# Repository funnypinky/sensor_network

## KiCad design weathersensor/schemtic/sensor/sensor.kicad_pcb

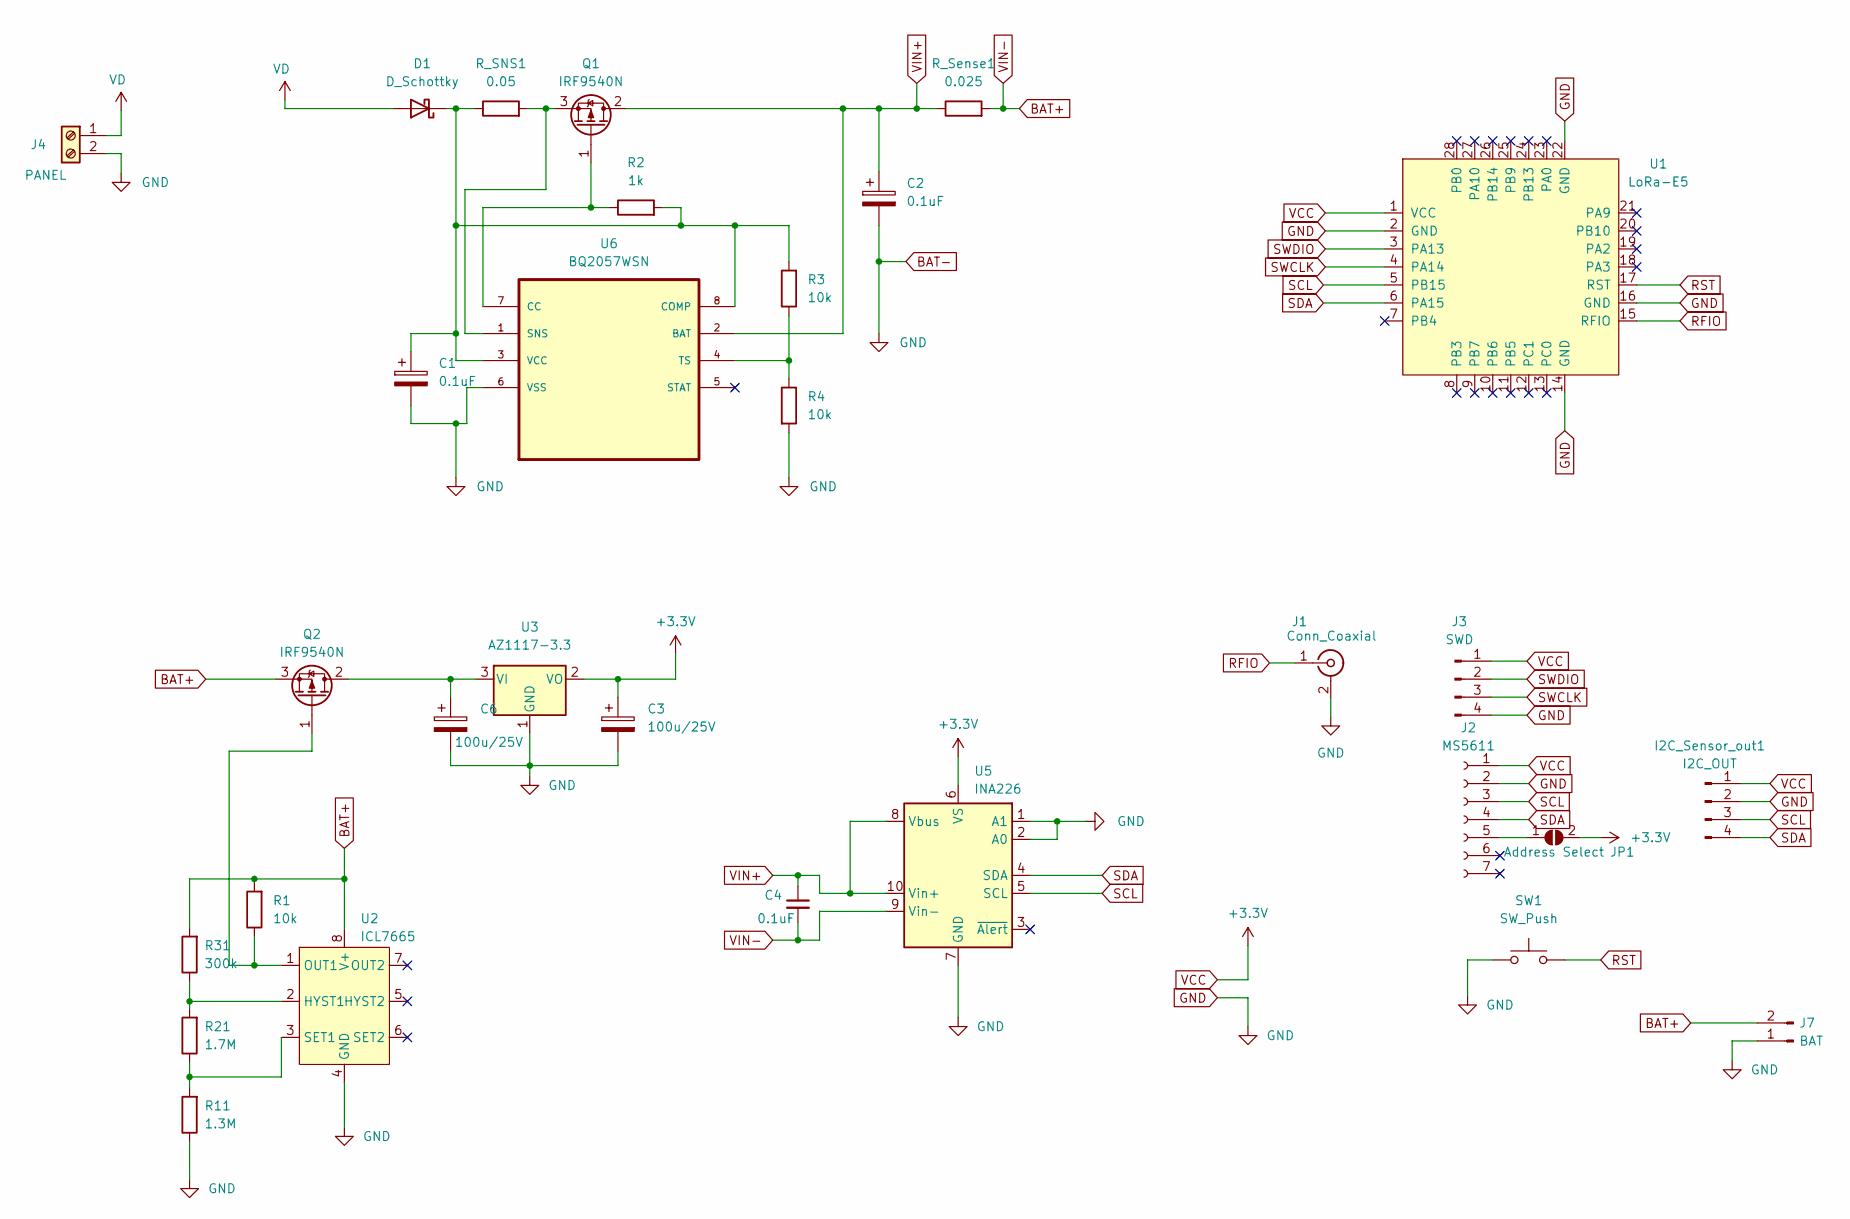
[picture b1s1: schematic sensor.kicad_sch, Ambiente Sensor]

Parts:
C1, C2, C4: 0.1uF; C_Rect_L4.6mm_W2.0mm_P2.50mm_MKS02_FKP02
C3, C6: 100u/25V; CP_Radial_D5.0mm_P2.50mm
D1: D_Schottky; D_SOD-123
I2C_Sensor_out1: I2C_OUT; JST_XH_B4B-XH-AM_1x04_P2.50mm_Vertical
J1: Conn_Coaxial; SMA_Amphenol_132203-12_Horizontal
J2: MS5611; PinHeader_1x07_P2.54mm_Vertical
J3: SWD; JST_XH_B4B-XH-AM_1x04_P2.50mm_Vertical
J4: PANEL; TerminalBlock_RND_205-00012_1x02_P5.00mm_Horizontal
J7: BAT; JST_EH_S2B-EH_1x02_P2.50mm_Horizontal
JP1: Address Select; SolderJumper-2_P1.3mm_Open_RoundedPad1.0x1.5mm
Q1, Q2: IRF9540N; TO-220-3_Horizontal_TabDown
R1, R3, R4: 10k; R_Axial_DIN0207_L6.3mm_D2.5mm_P10.16mm_Horizontal
R2: 1k; R_Axial_DIN0207_L6.3mm_D2.5mm_P10.16mm_Horizontal
R11: 1.3M; R_Axial_DIN0207_L6.3mm_D2.5mm_P10.16mm_Horizontal
R21: 1.7M; R_Axial_DIN0207_L6.3mm_D2.5mm_P10.16mm_Horizontal
R31: 300k; R_Axial_DIN0207_L6.3mm_D2.5mm_P10.16mm_Horizontal
R_SNS1: 0.05; R_2512_6332Metric
R_Sense1: 0.025; R_2512_6332Metric
SW1: SW_Push; SW_SPST_CK_RS282G05A3
U1: LoRa-E5
U2: ICL7665; DIP-8_W7.62mm_LongPads
U3: AZ1117-3.3; SOT-223
U5: INA226; VSSOP-10_3x3mm_P0.5mm
U6: BQ2057WSN; SOIC127P599X175-8N

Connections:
BAT+: C4.2, J7.2, Q2.3 (S), R1.2, R31.2, R_Sense1.2, U2.8 (V+), U5.9 (Vin-)
BAT-: C1.2, C2.2, C3.2, C6.2, I2C_Sensor_out1.2, J1.2 (Ext), J2.2, J3.4, J4.2, J7.1, R4.2, R11.1, SW1.1, U1.2 (GND), U1.14 (GND), U1.16 (GND), U1.22 (GND), U2.4 (GND), U3.1 (GND), U5.1 (A1), U5.2 (A0), U5.7 (GND), U6.6 (VSS)
unnamed: C1.1, D1.1 (K), R2.2, R3.2, R_SNS1.1, U6.3 (VCC), U6.8 (COMP)
unnamed: J2.5, JP1.1 (A)
unnamed: Q1.1 (G), R2.1, U6.7 (CC)
unnamed: Q1.3 (S), R_SNS1.2, U6.1 (SNS)
unnamed: C6.1, Q2.2 (D), U3.3 (VI)
unnamed: Q2.1 (G), R1.1, U2.1 (OUT1)
unnamed: R21.2, R31.1, U2.2 (HYST1)
unnamed: R11.2, R21.1, U2.3 (SET1)
unnamed: R3.1, R4.1, U6.4 (TS)
RFIO: J1.1 (In), U1.15 (RFIO)
RST: SW1.2, U1.17 (RST)
SCL: I2C_Sensor_out1.3, J2.3, U1.5 (PB15), U5.5 (SCL)
SDA: I2C_Sensor_out1.4, J2.4, U1.6 (PA15), U5.4 (SDA)
SWCLK: J3.3, U1.4 (PA14)
SWDIO: J3.2, U1.3 (PA13)
VCC: C3.1, I2C_Sensor_out1.1, J2.1, J3.1, JP1.2 (B), U1.1 (VCC), U3.2 (VO), U5.6 (VS)
VD: D1.2 (A), J4.1
VIN+: C2.1, C4.1, Q1.2 (D), R_Sense1.1, U5.8 (Vbus), U5.10 (Vin+), U6.2 (BAT)

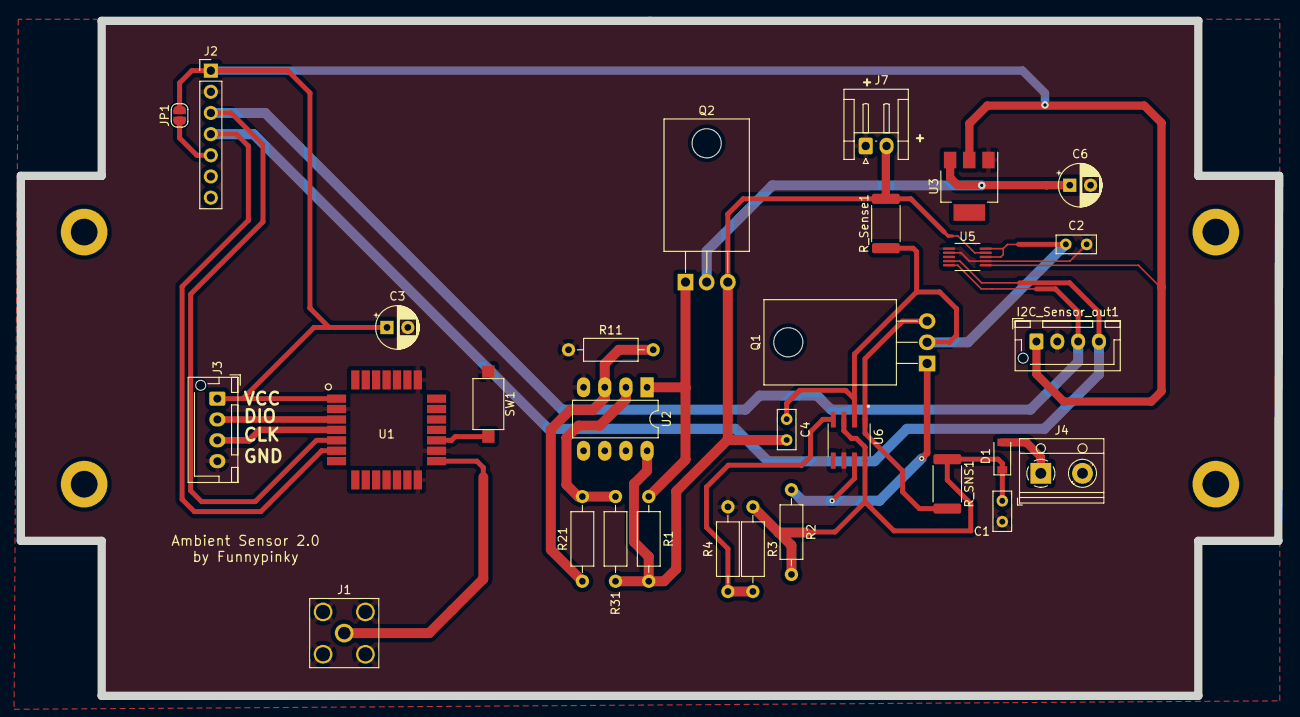
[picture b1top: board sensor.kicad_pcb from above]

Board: 2 copper layers, 151.0 x 81.0 mm, 30 parts (0 on the bottom side), 20 nets.

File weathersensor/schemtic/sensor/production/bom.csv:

Designator,Footprint,Quantity,Value,LCSC Part #
"C1, C2",1206,2,0.1u,
"C3, C6",C_Elec_6.3x7.7,2,100u/25V,
C4,1206,1,0.1uF,
D1,D_SOD-123,1,D_Schottky,
I2C_SENSOR_OUT1,JST_XH_B4B-XH-AM_1x04_P2.50mm_Vertical,1,I2C_OUT,
J1,SMA_Amphenol_132203-12_Horizontal,1,Conn_Coaxial,
J2,PinHeader_1x07_P2.54mm_Vertical,1,MS5611,
J3,JST_XH_B4B-XH-AM_1x04_P2.50mm_Vertical,1,SWD,
J4,TerminalBlock_RND_205-00012_1x02_P5.00mm_Horizontal,1,PANEL,
J7,JST_EH_S2B-EH_1x02_P2.50mm_Horizontal,1,BAT,
JP1,SolderJumper-2_P1.3mm_Open_RoundedPad1.0x1.5mm,1,Address Select,
"Q1, Q2",TO-263-2,2,IRF9540N,
"R1, R3, R4",2512,3,10k,
R11,2512,1,1.3M,
R2,2512,1,1k,
R21,2512,1,1.7M,
R31,2512,1,300k,
R_SENSE1,2512,1,0.025,
R_SNS1,2512,1,0.05,
SW1,SW_SPST_CK_RS282G05A3,1,SW_Push,
U1,LoRa-E5,1,LoRa-E5,
U2,SOIC-8_3.9x4.9mm_P1.27mm,1,ICL7665,
U3,SOT-223,1,AZ1117-3.3,
U5,VSSOP-10_3x3mm_P0.5mm,1,INA226,
U6,SOIC127P599X175-8N,1,BQ2057WSN,

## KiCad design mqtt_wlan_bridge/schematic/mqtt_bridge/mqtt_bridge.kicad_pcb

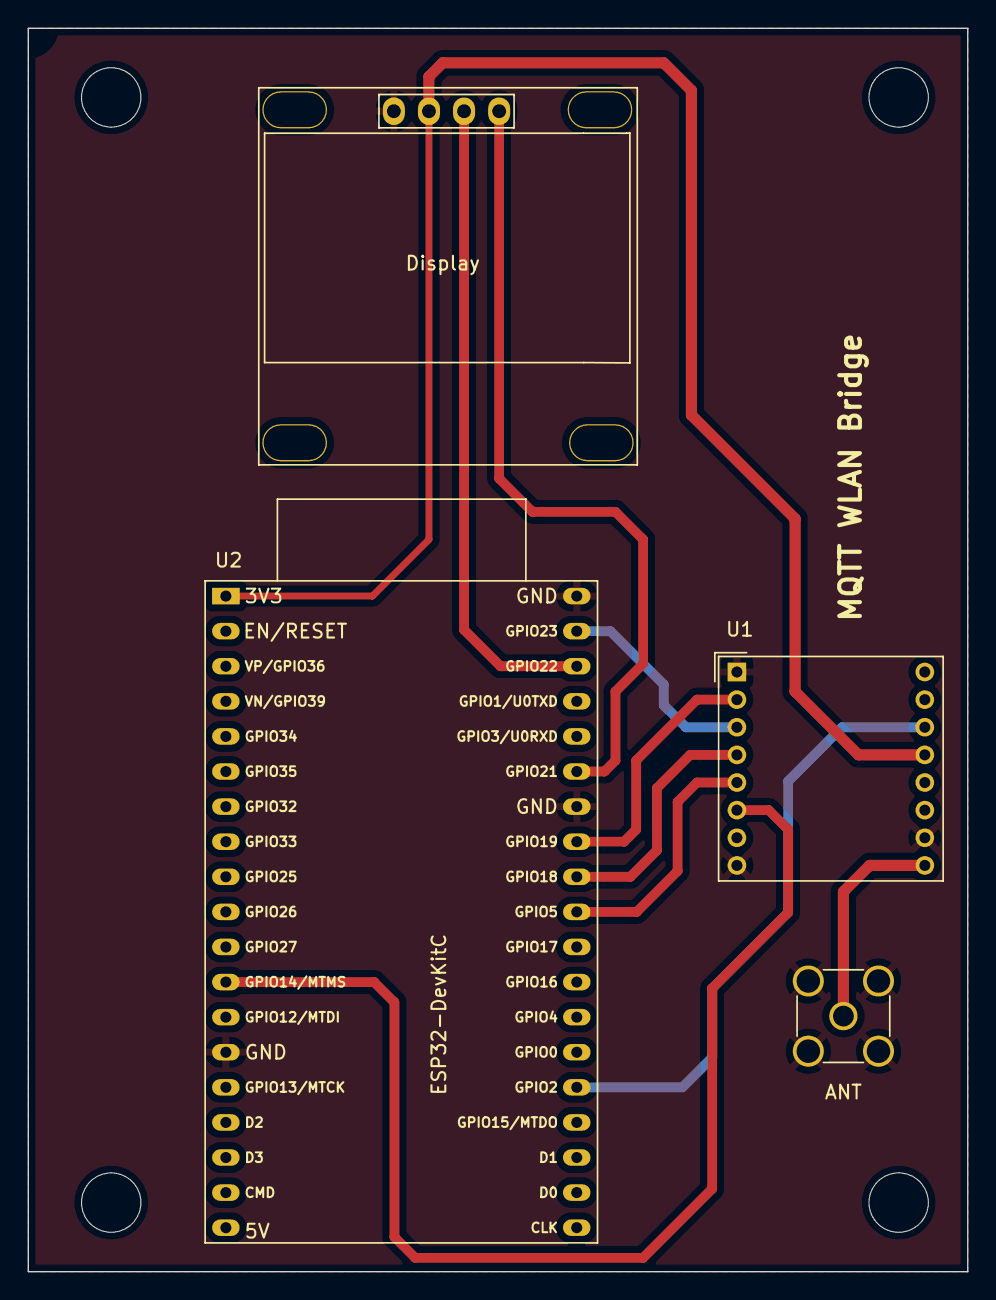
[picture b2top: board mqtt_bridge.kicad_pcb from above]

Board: 2 copper layers, 68.0 x 90.0 mm, 4 parts (0 on the bottom side), 11 nets.

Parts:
ANT: Conn_Coaxial; SMA_Amphenol_901-144_Vertical
Display: SSD1306; 128x64OLED
U1: RFM95W-868S2; HOPERF_RFM9XW_THT
U2: ESP32-DevKitC

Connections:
+3.3V: Display.2 (VCC), U1.13 (3.3V), U2.1 (3V3)
CLK: U1.4 (SCK), U2.30 (GPIO18)
DI0: U1.14 (DIO0), U2.24 (ADC2_CH2/*GPIO2)
GND: ANT.2 (Ext), Display.1 (GND), U1.1 (GND), U1.8 (GND), U1.10 (GND), U2.14 (GND), U2.32 (GND), U2.38 (GND)
MISO: U1.2 (MISO), U2.31 (GPIO19)
MOSI: U1.3 (MOSI), U2.37 (GPIO23)
NSS: U1.5 (NSS), U2.29 (*GPIO5)
unnamed: ANT.1 (In), U1.9 (ANT)
unnamed: U1.6 (RESET), U2.12 (MTMS/GPIO14/ADC2_CH6)
SCL: Display.3 (SCL), U2.36 (GPIO22)
SDA: Display.4 (SDA), U2.33 (GPIO21)

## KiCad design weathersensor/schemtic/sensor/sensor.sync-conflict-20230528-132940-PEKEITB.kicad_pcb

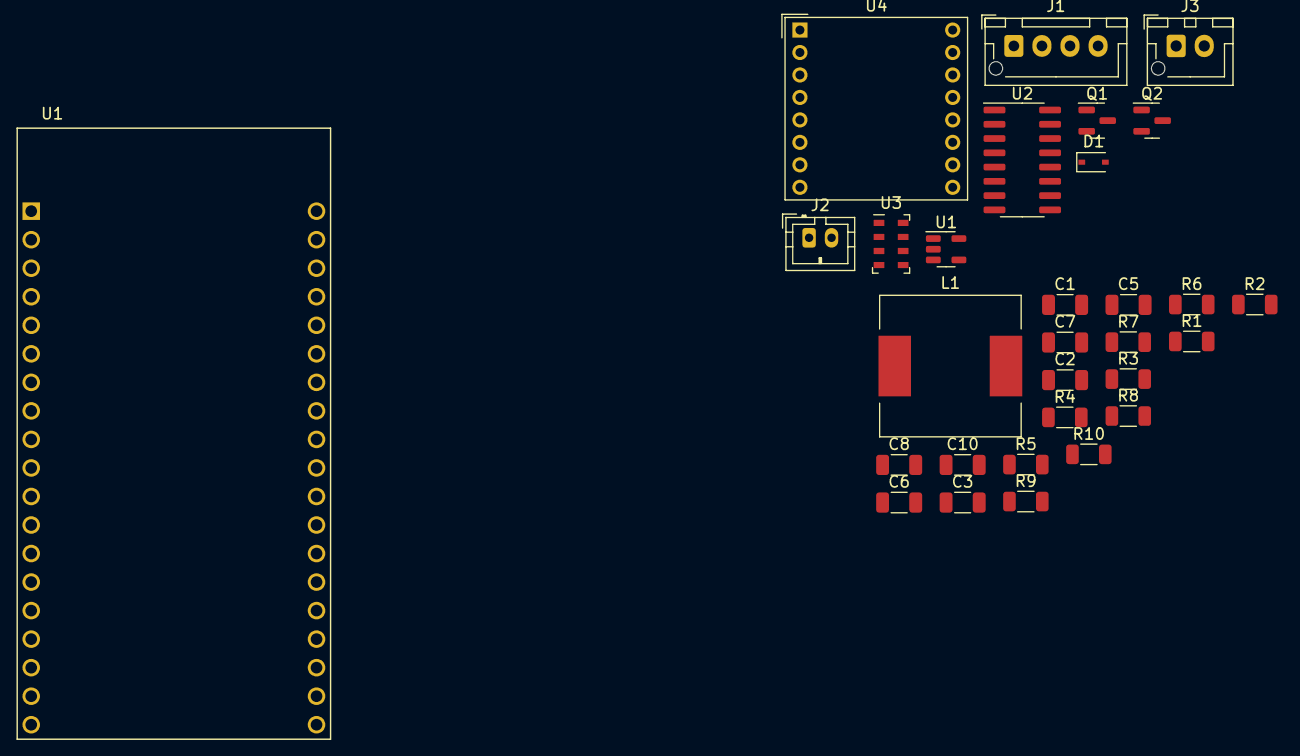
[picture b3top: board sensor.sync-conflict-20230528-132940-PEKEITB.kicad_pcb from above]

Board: 2 copper layers, 30 parts (0 on the bottom side), 12 nets, no tracks yet.

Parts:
C1, C2: 1.0u; C_1206_3216Metric
C3: 10u; C_1206_3216Metric
C5: 10n; C_1206_3216Metric
C6, C8: 100n; C_1206_3216Metric
C7: 22n; C_1206_3216Metric
C10: 220n; C_1206_3216Metric
D1: BAT60A; D_SOD-323
J1: Conn_01x04_Male; JST_XH_B4B-XH-AM_1x04_P2.50mm_Vertical
J2: Conn_01x02_Male; JST_PH_B2B-PH-K_1x02_P2.00mm_Vertical
J3: Conn_01x02_Male; JST_XH_B2B-XH-AM_1x02_P2.50mm_Vertical
L1: 82u; L_12x12mm_H8mm
Q1: IRLML6401; SOT-23
Q2: AO3401A; SOT-23
R1, R2: 10k; R_1206_3216Metric
R3, R4, R10: 1k; R_1206_3216Metric
R5: 120; R_1206_3216Metric
R6: 22k; R_1206_3216Metric
R7: 178k; R_1206_3216Metric
R8: 100; R_1206_3216Metric
R9: 0.05; R_1206_3216Metric
U1: XC6220B331MR; SOT-23-5
U1#2: ESP32-DEVKITC-32D; MODULE_ESP32-DEVKITC-32D
U2: CH340C; SOIC-16_3.9x9.9mm_P1.27mm
U3: MS5611-01BA; LGA-8_3x5mm_P1.25mm
U4: RFM95W-868S2; HOPERF_RFM9XW_THT

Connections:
+3.3V: C2.1, C3.1, R3.1, U1.5 (VOUT)
GND: C1.1, C2.2, C3.2, C5.2, C7.2, C8.2, C10.2, R1.2, R6.1, R10.1, U1.2 (GND)
unnamed: C7.1, R5.2
unnamed: C8.1, R8.1
unnamed: C1.2, D1.1 (K), Q1.2 (S), R2.1, U1.1 (VIN)
unnamed: R6.2, R7.1
unnamed: L1.2, R9.1
unnamed: R2.2, U1.3 (CE)
unnamed: U3.4 (CSB), U3.5 (CSB)
VSS: C5.1, C6.1, Q2.3 (D), R4.1, R7.2
V_BAT: C10.1, Q1.3 (D), R8.2, R9.2
V_USB: D1.2 (A), Q1.1 (G), R1.1

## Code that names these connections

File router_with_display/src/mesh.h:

#pragma once

#include <Wire.h>
#include <SPI.h>
#include <EEPROM.h>
#include <LoRa.h>
#include <ArduinoJson.h>
#include "hmi/hmi.hpp"
#include <PubSubClient.h>
#include <WiFi.h>

#define SCK 5   // GPIO5 -- SX127x's SCK
#define MISO 19 // GPIO19 -- SX127x's MISO
#define MOSI 27 // GPIO27 -- SX127x's MOSI
#define SS 13   // GPIO18 -- SX127x's CS
#define RST 14  // GPIO14 -- SX127x's RESET
#define DI0 25  // GPIO26 -- SX127x's IRQ (Interrupt Request)
#define BAND 868E6

void initMesh();
void updateRoutingTable();
void getRouteInfoString(char *p, size_t len);
void printNodeInfo(uint8_t node, char *s);
void collectRouteData();
void sendData(String data);
void recvData();
void onReceive(int packetSize);
void reconnect();

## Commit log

2022-01-28 Init repo
2022-01-28 Add readme
2022-01-28 move readme to correct folder
2022-02-18 Change png for display bug
2022-03-24 try radiohead example
2022-05-10 Alpha Version erreicht, Grundfunktionen laufen...Test auf Langzeitstabilität
2022-05-23 init
2023-02-22 Start commit message
    22.02.2023
    - add schematic and pcb for mqtt_wlan_bridge
    - remove old from git repo
    TODO:
    - create schematic and pcb for weathersensor
2023-02-22 Readme modify
2023-02-22 ignore OldFiles
2023-02-28 backup
2023-03-21 Start commit message
    21.03.2023
    - create and pcb for weathersensor
    22.02.2023
    - add schematic and pcb for mqtt_wlan_bridge
    - remove old from git repo
    TODO:
2023-06-20 Changes in Source Code:
    use the interal ADC for measure battery and panel voltage
2023-07-01 debugging
2024-01-03 Change sleep mode
2024-01-03 Change Library from LoRa to RadioLib
2024-08-22 Commit before fork
2024-09-11 Change to lorawan
2024-11-01 Added Sensor HYT221
2025-05-06 Änderung des Sensor auf neue Plattform STM32WLxx Lora-e5
2025-05-06 Change gitignore
2025-05-06 Ignore backups from KiCad
